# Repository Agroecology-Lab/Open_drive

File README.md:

# Open Drive

Dual-motor BLDC / FOC controller. Compatible with ODrive 3.5 and SimpleFOC.

## Specification

| | |
|---|---|
| Motor channels | 2 (M0, M1), 3-phase each |
| MCU | STM32F405RGT7, LQFP-64, 8 MHz ceramic resonator (Y1) |
| Gate drivers | 2 × DRV8301 (U1 = M0, U2 = M1), SPI-configured |
| Power stage | 12 × IRF7480M DirectFET N-MOSFET (6 per motor) |
| Current sense | 4 × 0.5 mΩ 2512 shunts (R12, R16, R32, R36), DRV8301 amplifiers |
| Supply | XT30 (J3), silk-marked MAX 48 V |
| Bulk capacitance | 10 µF 50 V 1206 array on bottom side |
| Logic supply | 5 V from DRV8301 (U1) buck (L1, D1); 3.3 V from U4 (SPX3819); 3.3 VA analog from U5 (LP5907) |
| USB | USB-C (J4), USBLC6-2SC6 ESD (U8); VBUS via F1 (500 mA) and D4 into +5 V |
| CAN | SN65HVD232 transceiver (U7), two connectors (J7, J8) |
| Auxiliary half-bridge | Q13, Q14 (CSD18540Q5B), LM5109B driver (U3); AUX_H / AUX_L from MCU; switch node `HS` on pad H6 |
| Temperature | 3 × 10 k NTC (TH1–TH3): M0_TEMP, M1_TEMP, AUX_TEMP |
| PCB | 4 layers, 1.6 mm, approx. 85.5 × 56 mm, 4 × mounting holes |
| Assembly | JLCPCB, both sides |

Firmware is not included in this repository.

## Connectors

| Ref | Silk | Type | Pins |
|---|---|---|---|
| J3 | MAX 48V | XT30PW | 1 GND, 2 VDC |
| J1 | M0 | MR30PW 3-pole | phases A, B, C |
| J2 | M1 | MR30PW 3-pole | phases A, B, C |
| J10 | ENC0 | JST SH 5-pin | 1 GND, 2 +5 V, 3 A, 4 B, 5 Z |
| J11 | ENC1 | JST SH 5-pin | 1 GND, 2 +5 V, 3 A, 4 B, 5 Z |
| J4 | USB | USB-C | USB 2.0, DFU / serial via STM32 |
| J5 | Serial | JST SH 3-pin | 1 GPIO_1, 2 GPIO_2, 3 GND |
| J6 | GPIO | JST SH 6-pin | 1–6 = GPIO_3 … GPIO_8 |
| J7 | CAN2 | JST SH 2-pin | 1 CAN_H, 2 CAN_L |
| J8 | CAN1 | JST SH 2-pin | 1 CAN_H, 2 CAN_L |
| J9 | DEBUG | JST SH 4-pin | 1 +5 V, 2 SWDIO, 3 SWCLK, 4 GND |

Bottom side also has solder pads for power (+ / −) and for each motor (U, V, W).

## Indicators and controls

- SW1 (DFU): pulls BOOT0 to 3.3 V. Hold while powering to enter the STM32 DFU bootloader.
- D3: green LED.
- Test pads (top, right): nFAULT, VCC, AVCC, 5V.
- TP4, TP5: test points near J4.

## Schematic

[Open_Drive_Schematic.pdf](Open_Drive_Schematic.pdf). KiCad sheets in `bldc_motor_cntroller/`:

| Sheet | Contents |
|---|---|
| `bldc_motor_cntroller.sch` | Top level |
| `microcontroller_interface.sch` | STM32F405 |
| `motor_driver.sch` | M0 DRV8301 and power stage |
| `motor_driver2.sch` | M1 DRV8301 and power stage |
| `power_management.sch` | Buck, LDOs, auxiliary half-bridge |
| `io_interface.sch` | USB, CAN, encoders, GPIO, debug |

## Repository layout

```
bldc_motor_cntroller/
  *.sch, *.kicad_pcb, *.pro   KiCad project
  outputs/gerbers/            Gerber and drill files
  assembly/                   BOM and placement (KiCad export)
  production/                 JLCPCB BOM, placement, netlist, order zip
  bom/ibom.html               Interactive BOM
  images/                     Board renders
Open_Drive_Schematic.pdf
```

## Ordering

1. Upload `bldc_motor_cntroller/outputs/gerbers/` (or `production/bldc_motor_cntroller.zip`) to JLCPCB, 4 layers, 1.6 mm.
2. Enable assembly, both sides. Upload the BOM and positions files from `production/`.
3. Check part rotation in the JLCPCB PCBA viewer before ordering. Rotation of SW1 and U4 differs from the KiCad export.

## Attribution

Based on [X_driver](https://github.com/dj140/X_driver) by Dj140, which is based on the ODrive 3.5 schematic.

## License

GPL-3.0. See [LICENSE](LICENSE).

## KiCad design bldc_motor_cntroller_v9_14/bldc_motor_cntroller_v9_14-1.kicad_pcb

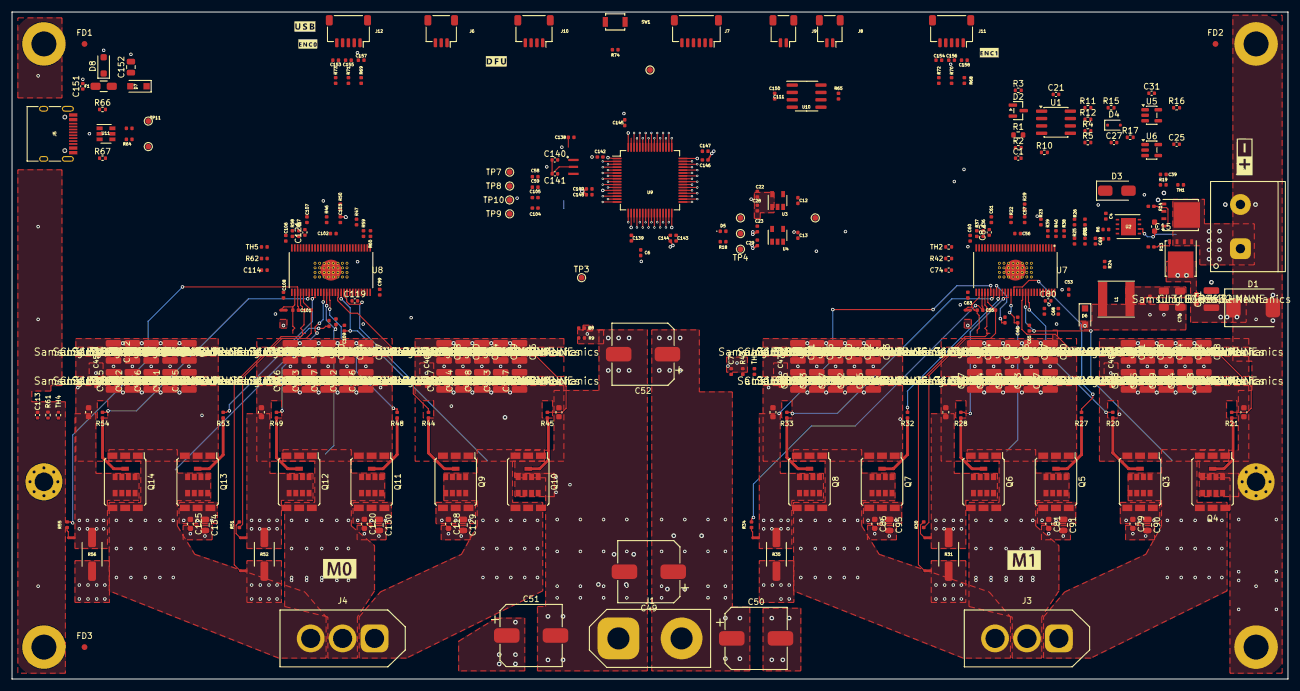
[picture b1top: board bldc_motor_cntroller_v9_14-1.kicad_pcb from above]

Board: 4 copper layers, 220.0 x 115.0 mm, 329 parts (0 on the bottom side), 165 nets.

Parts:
C1: 100pF 50V; C_0402_1005Metric
C2, C3, C5, C7, C8, C9, C10, C11, C14, C16, C17, C18, C19, C20, C24, C26, C30, C32, C33, C34, C35, C36, C37, C38, C40, C41, C42, C43, C44, C71, C76, C77, C78, C83, C84, C85, C87, C88, C89, C92, C93, C94, C96, C97, C98, C112, C115, C116, C117, C122, C123, C124, C126, C127, C128, C131, C132, C133, C135, C136, C137: 4.7uF 100V; C_1210_3225Metric
C4, C57, C74, C75, C103, C113, C114: 2.2uF 25V; C_0402_1005Metric
C6, C73: 270pF 50V; C_0402_1005Metric
C12, C13, C22, C23, C60, C61, C72, C106, C107, C149: 1uF 25V; C_0402_1005Metric
C15: 470nF 50V; C_0603_1608Metric
C21, C25, C31, C138: 100nF 16V; C_0402_1005Metric
C27: 470pF 50V; C_0402_1005Metric
C28, C29: 0.1uF 16V; C_0402_1005Metric
C39, C144, C146: 2.2uF 16V; C_0402_1005Metric
C45, C46, C47, C48, C62, C63, C65, C66, C67, C68, C80, C82, C108, C119, C121, C151: 100nF 50V; C_0402_1005Metric
C49, C50, C51, C52: 100uF 100V; CP_Elec_10x10.5
C53, C99: 15nF 50V; C_0402_1005Metric
C54, C55, C58, C59, C100, C101, C104, C105: 2.2nF 50V; C_0402_1005Metric
C56, C102: 22nF 50V; C_0402_1005Metric
C64, C70: 47uF 16V; C_1206_3216Metric
C69: 82pF 50V; C_0402_1005Metric
C79, C81, C86, C118, C120, C125: 100nF 100V; C_0603_1608Metric
C90, C91, C95, C129, C130, C134: 1uF 100V; C_0805_2012Metric
C109, C110, C111: 0.1uF 50V; C_0402_1005Metric
C139, C142, C143, C145, C147, C148, C150, C153, C154, C155, C156, C157, C158: 100nF; C_0402_1005Metric
C140, C141: 12pF; C_0402_1005Metric
C152: 4.7uF 25V; C_0805_2012Metric
C_AUX1: 100nF 100V; C_0603_1608Metric
C_HF1, C_HF2, C_HF3, C_HF4, C_HF5, C_HF6: 100nF 100V; C_0603_1608Metric
D1: 5.0SMDJ48A; D_SMC
D2: LM4040C25IDBZR; SOT-23
D3: STPS1H100A; D_SMA
D4: BAT54J; D_SOD-323F
D5: GREEN; LED_0402_1005Metric
D6, D7: MBR2H100SFT3G; D_SOD-123F
D8: SMF5.0A; D_SOD-123F
F1: Fuse_500MA; Fuse_1206_3216Metric
FD1, FD2, FD3: Fiducial; Fiducial_1mm_Mask2mm
G1: LOGO; M00
G2: LOGO; M1
G3: LOGO; batt
G4: LOGO; DFU
G5: LOGO; USB
G6: LOGO; ENC0
G7: LOGO; ENC1
H1, H4: MountingHole_3.2mm_M3_Pad_Via
H2, H3, H5, H6: MountingHole_Pad; MountingHole_4.3mm_M4_Pad
J1: XT90; AMASS_XT90-M_1x02_P10.90mm_Vertical
J2: DB910-7.62-2P-GN-S; DORABO_DB910-7.62-2P
J3, J4: MR60PB-M 30A (60A); AMASS_MR60PB-M_1x03_P5.50mm_Vertical
J5: USB_C_Receptacle_USB2.0; USB_C_Receptacle_HRO_TYPE-C-31-M-12
J6: Conn_01x03; JST_SH_SM03B-SRSS-TB_1x03-1MP_P1.00mm_Horizontal
J7: Conn_01x06; JST_SH_SM06B-SRSS-TB_1x06-1MP_P1.00mm_Horizontal
J8, J9: Conn_01x02; JST_SH_SM02B-SRSS-TB_1x02-1MP_P1.00mm_Horizontal
J10: Conn_01x04; JST_SH_SM04B-SRSS-TB_1x04-1MP_P1.00mm_Horizontal
J11, J12: Conn_01x05; JST_SH_SM05B-SRSS-TB_1x05-1MP_P1.00mm_Horizontal
L1: 33uH 1.4A; L_Taiyo-Yuden_NR-60xx
NT1, NT2, NT3, NT4, NT5, NT6, NT7, NT8: Net-Tie_2; NetTie-2_SMD_Pad0.5mm
Q1, Q2: CSD18540Q5B; TDSON-8-1
Q3, Q4, Q5, Q6, Q7, Q8, Q9, Q10, Q11, Q12, Q13, Q14: IRF7759L2TRPBF; DirectFET_L8
R1: 180k; R_0603_1608Metric
R2, R4, R5, R38, R39, R40, R59, R60, R74: 10k; R_0402_1005Metric
R3, R9, R15, R18, R22, R46: 1k; R_0402_1005Metric
R6, R7, R19, R26, R29, R42, R43, R50, R61, R62, R68, R69, R70, R71, R72, R73: 3.3k; R_0402_1005Metric
R8, R23, R25, R47: 18k; R_0402_1005Metric
R10: 330k; R_0402_1005Metric
R11, R12: 4.7k; R_0402_1005Metric
R13, R14, R20, R21, R27, R28, R32, R33, R44, R45, R48, R49, R53, R54: 2R2; R_0402_1005Metric
R16, R17: 100k; R_0402_1005Metric
R24: 220k 1%; R_0402_1005Metric
R30, R34, R51, R55, R65: 120R; R_0402_1005Metric
R31, R35, R52, R56: 500uOhm 6W 1%; R_2512_6332Metric
R36, R37, R57, R58, R63, R64: 22R 1%; R_0402_1005Metric
R41: 47k 1%; R_0402_1005Metric
R66, R67: 5.1k 1%; R_0402_1005Metric
SW1: B3U-1000P-B; SW_SPST_B3U-1000P
TH1, TH2, TH3, TH4, TH5: 10k; R_0402_1005Metric
TP1, TP2, TP3, TP4, TP5, TP6, TP7, TP8, TP9, TP10, TP11, TP12: TestPoint; TestPoint_Pad_D1.0mm
U1: LM393BIDR; SOIC-8_3.9x4.9mm_P1.27mm
U2: LM5109BSD; WSON-8_4x4mm_P0.8mm
U3: SPX3819M5-L-3-3; SOT-23-5
U4: LP5907MFX-3.3; SOT-23-5
U5: SN74LVC1G32DBVR; SOT-23-5
U6: SN74LVC1G08DBVR; SOT-23-5
U7, U8: DRV8301DCAR; DRV8301DCA_v9
U9: STM32F405RGTx; LQFP-64_10x10mm_P0.5mm
U10: SN65HVD232; SOIC-8_3.9x4.9mm_P1.27mm
U11: USBLC6-2SC6; SOT-23-6
Y1: CSTCE8M00G55-R0

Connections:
+3.3V: C21.1, C22.1, C25.1, C28.1, C31.1, C80.1, C119.1, C139.1, C142.1, C143.1, C145.1, C147.1, C150.2, D5.1, R3.1, R4.1, R11.1, R12.1, R38.2, R39.2, R40.2, R59.2, R60.2, R68.1, R69.1, R70.1, R71.1, R72.1, R73.1, SW1.1, TP1.1, U1.8, U3.5, U5.5, U6.5, U7.49, U8.49, U9.1, U9.19, U9.32, U9.48, U9.64, U10.3
+3.3VA: C23.1, C29.1, C82.1, C121.1, C148.1, C149.1, TH1.1, TH2.1, TH3.1, TH4.1, TH5.1, TP2.1, U4.5, U7.24, U8.24, U9.13
+5V: C12.1, C13.1, C64.1, C70.1, C72.1, D7.1, J10.1, J11.2, J12.2, L1.2, R25.2, TP5.1, U3.1, U3.3, U4.1, U4.3, U11.5
/I/O Interface/BOOT0: R74.2, SW1.2, U9.60
/I/O Interface/CAN_D: U9.62, U10.1
/I/O Interface/CAN_R: U9.61, U10.4
/I/O Interface/DEBUG_SWCLK: J10.3, U9.49
/I/O Interface/DEBUG_SWDIO: J10.2, U9.46
/I/O Interface/ENC0_A: C154.2, J11.3, R72.2, U9.56
/I/O Interface/ENC0_B: C156.2, J11.4, R70.2, U9.57
/I/O Interface/ENC0_Z: C158.2, J11.5, R68.2, U9.40
/I/O Interface/ENC1_A: C153.2, J12.3, R73.2, U9.58
/I/O Interface/ENC1_B: C155.2, J12.4, R71.2, U9.59
/I/O Interface/ENC1_Z: C157.2, J12.5, R69.2, U9.4
/I/O Interface/GPIO_1: J6.1, U9.14
/I/O Interface/GPIO_2: J6.2, U9.15
/I/O Interface/GPIO_3: J7.1, U9.16
/I/O Interface/GPIO_4: J7.2, U9.17
/I/O Interface/GPIO_5: J7.3, U9.24
/I/O Interface/GPIO_6: J7.4, U9.28
/I/O Interface/GPIO_7: J7.5, U9.50
/I/O Interface/GPIO_8: J7.6, U9.55
/I/O Interface/USB_CC1: J5.A5, R66.1
/I/O Interface/USB_CC2: J5.B5, R67.1
/I/O Interface/USB_DN: R63.1, TP11.1, U9.44
/I/O Interface/USB_DP: R64.1, TP12.1, U9.45
/I/O Interface/USB_J4_DN: J5.A7, J5.B7, R63.2, U11.1, U11.6
/I/O Interface/USB_J4_DP: J5.A6, J5.B6, R64.2, U11.3, U11.4
/I/O Interface/USB_VBUS_PROT: C152.1, D7.2, D8.1, F1.2
/I/O Interface/USB_VBUS_RAW: C151.1, F1.1, J5.A4, J5.A9, J5.B4, J5.B9
/Microcontroller Interface/AUX_TEMP: C39.1, R19.2, TH1.2, U9.21
/Microcontroller Interface/EN_GATE: R22.2, R46.2, U7.16, U8.16, U9.33
/Microcontroller Interface/M0_AH: U7.17, U9.41
/Microcontroller Interface/M0_AL: U7.18, U9.34
/Microcontroller Interface/M0_BH: U7.19, U9.42
/Microcontroller Interface/M0_BL: U7.20, U9.35
/Microcontroller Interface/M0_CH: U7.21, U9.43
/Microcontroller Interface/M0_CL: U7.22, U9.36
/Microcontroller Interface/M0_SO1: C58.2, R36.2, TP7.1, U9.8
/Microcontroller Interface/M0_SO2: C59.2, R37.2, TP8.1, U9.9
/Microcontroller Interface/M0_TEMP: C75.1, R43.2, TH3.2, U9.25
/Microcontroller Interface/M1_AH: U8.17, U9.37
/Microcontroller Interface/M1_AL: U8.18, U9.23
/Microcontroller Interface/M1_BH: U8.19, U9.38
/Microcontroller Interface/M1_BL: U8.20, U9.26
/Microcontroller Interface/M1_CH: U8.21, U9.39
/Microcontroller Interface/M1_CL: U8.22, U9.27
/Microcontroller Interface/M1_SO1: C104.2, R57.2, TP9.1, U9.11
/Microcontroller Interface/M1_SO2: C105.2, R58.2, TP10.1, U9.10
/Microcontroller Interface/M1_TEMP: C114.1, R62.2, TH5.2, U9.20
/Microcontroller Interface/SPI_M0_nCS: U7.8, U9.2
/Microcontroller Interface/SPI_M1_nCS: U8.8, U9.3
/Microcontroller Interface/SPI_MISO: U7.10, U8.10, U9.52
/Microcontroller Interface/SPI_MOSI: U7.9, U8.9, U9.53
/Microcontroller Interface/SPI_SCK: U7.11, U8.11, U9.51
/Microcontroller Interface/VBUS_S: C6.1, R8.2, R9.1, U9.22
/Microcontroller Interface/nFAULT: R39.1, R59.1, TP6.1, U7.6, U8.6, U9.54
/Motor Driver/AVDD: C60.1, U7.27
/Motor Driver/DVDD: C61.1, U7.23
/Motor Driver/GH_A: R20.1, U7.47
/Motor Driver/GH_B: R27.1, U7.42
/Motor Driver/GH_C: R32.1, U7.37
/Motor Driver/GL_A: R21.1, U7.45
/Motor Driver/GL_B: R28.1, U7.40
/Motor Driver/GL_C: R33.1, U7.35
/Motor Driver/PWRGD: R38.1, U7.4
/Motor Driver/SH_A: C65.1, J3.1, Q3.3, Q4.1, U7.46
/Motor Driver/SH_B: C66.1, J3.2, Q5.3, Q6.1, U7.41
/Motor Driver/SH_C: C67.1, J3.3, Q7.3, Q8.1, U7.36
/Motor Driver/SL_B: C_HF2.2, NT1.2, Q6.3, R31.2, U7.39
/Motor Driver/SL_C: C_HF3.2, NT3.2, Q8.3, R35.2, U7.34
/Motor Driver/SN1: C54.2, R30.1, U7.33
/Motor Driver/SN2: C55.2, R34.1, U7.31
/Motor Driver/SP1: C54.1, NT2.1, U7.32
/Motor Driver/SP2: C55.1, NT4.1, U7.30
/Motor Driver/TEMP_SENSE_2: C74.1, R42.2, TH2.2
/Motor Driver/nOCTW: R40.1, U7.5
/Motor_Driver2/AVDD: C106.1, U8.27
/Motor_Driver2/DVDD: C107.1, U8.23
/Motor_Driver2/GH_A: R44.1, U8.47
/Motor_Driver2/GH_B: R48.1, U8.42
/Motor_Driver2/GH_C: R53.1, U8.37
/Motor_Driver2/GL_A: R45.1, U8.45
/Motor_Driver2/GL_B: R49.1, U8.40
/Motor_Driver2/GL_C: R54.1, U8.35
/Motor_Driver2/SH_A: C109.1, J4.1, Q9.3, Q10.1, U8.46
/Motor_Driver2/SH_B: C110.1, J4.2, Q11.3, Q12.1, U8.41
/Motor_Driver2/SH_C: C111.1, J4.3, Q13.3, Q14.1, U8.36
/Motor_Driver2/SL_B: C_HF5.2, NT5.2, Q12.3, R52.2, U8.39
/Motor_Driver2/SL_C: C_HF6.2, NT7.2, Q14.3, R56.2, U8.34
/Motor_Driver2/SN1: C100.2, R51.1, U8.33
/Motor_Driver2/SN2: C101.2, R55.1, U8.31
/Motor_Driver2/SP1: C100.1, NT6.1, U8.32
/Motor_Driver2/SP2: C101.1, NT8.1, U8.30
/Motor_Driver2/TEMP_SENSE_2: C113.1, R61.2, TH4.2
/Motor_Driver2/nOCTW: R60.1, U8.5
/Power Management/HS: C15.2, J2.1, Q1.1, Q1.2, Q1.3, Q2.5, U2.6
/Power Management/OVP_ACTIVE: D4.1, R10.2, R11.2, R15.1, U1.1, U1.6
/Power Management/OVP_ACTIVE_DLY: C27.1, D4.2, R15.2, U5.2
/Power Management/OVP_VMID: R4.2, R5.1, U1.5
/Power Management/OVP_VREF: D2.1, R3.2, U1.2
/Power Management/OVP_VSENSE: C1.1, R1.2, R2.1, R10.1, U1.3
/Power Management/nOVP_ACTIVE: R12.2, U1.7, U6.2
CAN_H: J8.1, J9.1, R65.2, U10.7
CAN_L: J8.2, J9.2, R65.1, U10.6
GND: C1.2, C2.2, C3.2, C4.2, C5.2, C6.2, C7.2, C8.2, C9.2, C10.2, C11.2, C12.2, C13.2, C14.2, C16.2, C17.2, C18.2, C19.2, C20.2, C21.2, C22.2, C23.2, C24.2, C25.2, C26.2, C27.2, C28.2, C29.2, C30.2, C31.2, C32.2, C33.2, C34.2, C35.2, C36.2, C37.2, C38.2, C39.2, C40.2, C41.2, C42.2, C43.2, C44.2, C45.2, C46.2, C47.2, C48.2, C49.2, C50.2, C51.2, C52.2, C53.1, C57.2, C58.1, C59.1, C60.2, C61.2, C63.2, C64.2, C68.2, C69.2, C70.2, C71.2, C72.2, C73.2, C74.2, C75.2, C76.2, C77.2, C78.2, C79.2, C80.2, C81.2, C82.2, C83.2, C84.2, C85.2, C86.2, C87.2, C88.2, C89.2, C90.2, C91.2, C92.2, C93.2, C94.2, C95.2, C96.2, C97.2, C98.2, C99.1, C103.2, C104.1, C105.1, C106.2, C107.2, C108.2, C112.2, C113.2, C114.2, C115.2, C116.2, C117.2, C118.2, C119.2, C120.2, C121.2, C122.2, C123.2, C124.2, C125.2, C126.2, C127.2, C128.2, C129.2, C130.2, C131.2, C132.2, C133.2, C134.2, C135.2, C136.2, C137.2, C138.2, C139.2, C140.1, C141.1, C142.2, C143.2, C144.2, C145.2, C146.2, C147.2, C148.2, C149.2, C150.1, C151.2, C152.2, C153.1, C154.1, C155.1, C156.1, C157.1, C158.1, C_AUX1.2, C_HF1.2, C_HF4.2, D1.2, D2.2, D6.2, D8.2, H1.1 (1_1), H2.1 (1_1), H3.1 (1_1), H4.1 (1_1), H5.1 (1_1), H6.1 (1_1), J1.1, J2.2, J5.A1, J5.A12, J5.B1, J5.B12, J5.S1, J6.3, J10.4, J11.1, J12.1, NT2.2, NT4.2, NT6.2, NT8.2, Q2.1, Q2.2, Q2.3, Q4.3, Q10.3, R2.2, R5.2, R6.1, R7.1, R9.2, R16.2, R17.2, R18.2, R19.1, R22.1, R23.2, R24.2, R26.1, R29.1, R31.1, R35.1, R42.1, R43.1, R46.1, R47.2, R50.1, R52.1, R56.1, R61.1, R62.1, R66.2, R67.2, R74.1, TP4.1, U1.4, U2.4, U2.9, U3.2, U4.2, U5.3, U6.3, U7.28, U7.44, U7.57, U8.28, U8.44, U8.55, U8.57, U9.12, U9.18, U9.63, U10.2, U11.2, Y1.3
GVDD: C4.1, C57.1, C103.1, D3.2, TP3.1, U2.1, U7.13, U8.13
unnamed: C73.1, R41.2
unnamed: C15.1, D3.1, U2.8
unnamed: D5.2, R18.1
unnamed: C62.1, D6.1, L1.1, U7.50, U7.51
unnamed: NT1.1, R30.2
unnamed: NT3.1, R34.2
unnamed: NT5.1, R51.2
unnamed: NT7.1, R55.2
unnamed: Q1.4, R13.1
unnamed: Q2.4, R14.1
unnamed: Q3.2, R20.2
unnamed: Q4.2, R21.2
unnamed: Q5.2, R27.2
unnamed: Q6.2, R28.2
unnamed: Q7.2, R32.2
unnamed: Q8.2, R33.2
unnamed: Q9.2, R44.2
unnamed: Q10.2, R45.2
unnamed: Q11.2, R48.2
unnamed: Q12.2, R49.2
unnamed: Q13.2, R53.2
unnamed: Q14.2, R54.2
unnamed: R13.2, U2.7
unnamed: R14.2, U2.5
unnamed: C65.2, U7.48
unnamed: C66.2, U7.43
unnamed: C62.2, U7.52
unnamed: C67.2, U7.38
unnamed: C69.1, R41.1, U7.2
unnamed: C56.1, U7.14
unnamed: C56.2, U7.15
unnamed: R29.2, U7.12
unnamed: R23.1, U7.7
unnamed: R24.1, U7.1
unnamed: R36.1, U7.25
unnamed: R37.1, U7.26
unnamed: C53.2, U7.56
unnamed: R25.1, R26.2, U7.3
unnamed: C109.2, U8.48
unnamed: C110.2, U8.43
unnamed: C111.2, U8.38
unnamed: C102.1, U8.14
unnamed: C102.2, U8.15
unnamed: R50.2, U8.12
unnamed: R47.1, U8.7
unnamed: R57.1, U8.25
unnamed: R58.1, U8.26
unnamed: C99.2, U8.56
unnamed: C138.1, U9.7
unnamed: C140.2, U9.5, Y1.1
unnamed: C141.2, U9.6, Y1.2
unnamed: C144.1, U9.31
unnamed: C146.1, U9.47
OVP_IN_HI: R16.1, U5.1, U9.30
OVP_IN_LI: R17.1, U6.1, U9.29
U3_HI_DRV: R6.2, U2.2, U5.4
U3_LI_DRV: R7.2, U2.3, U6.4
VDC: C2.1, C3.1, C5.1, C7.1, C8.1, C9.1, C10.1, C11.1, C14.1, C16.1, C17.1, C18.1, C19.1, C20.1, C24.1, C26.1, C30.1, C32.1, C33.1, C34.1, C35.1, C36.1, C37.1, C38.1, C40.1, C41.1, C42.1, C43.1, C44.1, C45.1, C46.1, C47.1, C48.1, C49.1, C50.1, C51.1, C52.1, C63.1, C68.1, C71.1, C76.1, C77.1, C78.1, C79.1, C81.1, C83.1, C84.1, C85.1, C86.1, C87.1, C88.1, C89.1, C90.1, C91.1, C92.1, C93.1, C94.1, C95.1, C96.1, C97.1, C98.1, C108.1, C112.1, C115.1, C116.1, C117.1, C118.1, C120.1, C122.1, C123.1, C124.1, C125.1, C126.1, C127.1, C128.1, C129.1, C130.1, C131.1, C132.1, C133.1, C134.1, C135.1, C136.1, C137.1, C_AUX1.1, C_HF1.1, C_HF2.1, C_HF3.1, C_HF4.1, C_HF5.1, C_HF6.1, D1.1, J1.2, Q1.5, Q3.1, Q5.1, Q7.1, Q9.1, Q11.1, Q13.1, R1.1, R8.1, U7.29, U7.53, U7.54, U8.29

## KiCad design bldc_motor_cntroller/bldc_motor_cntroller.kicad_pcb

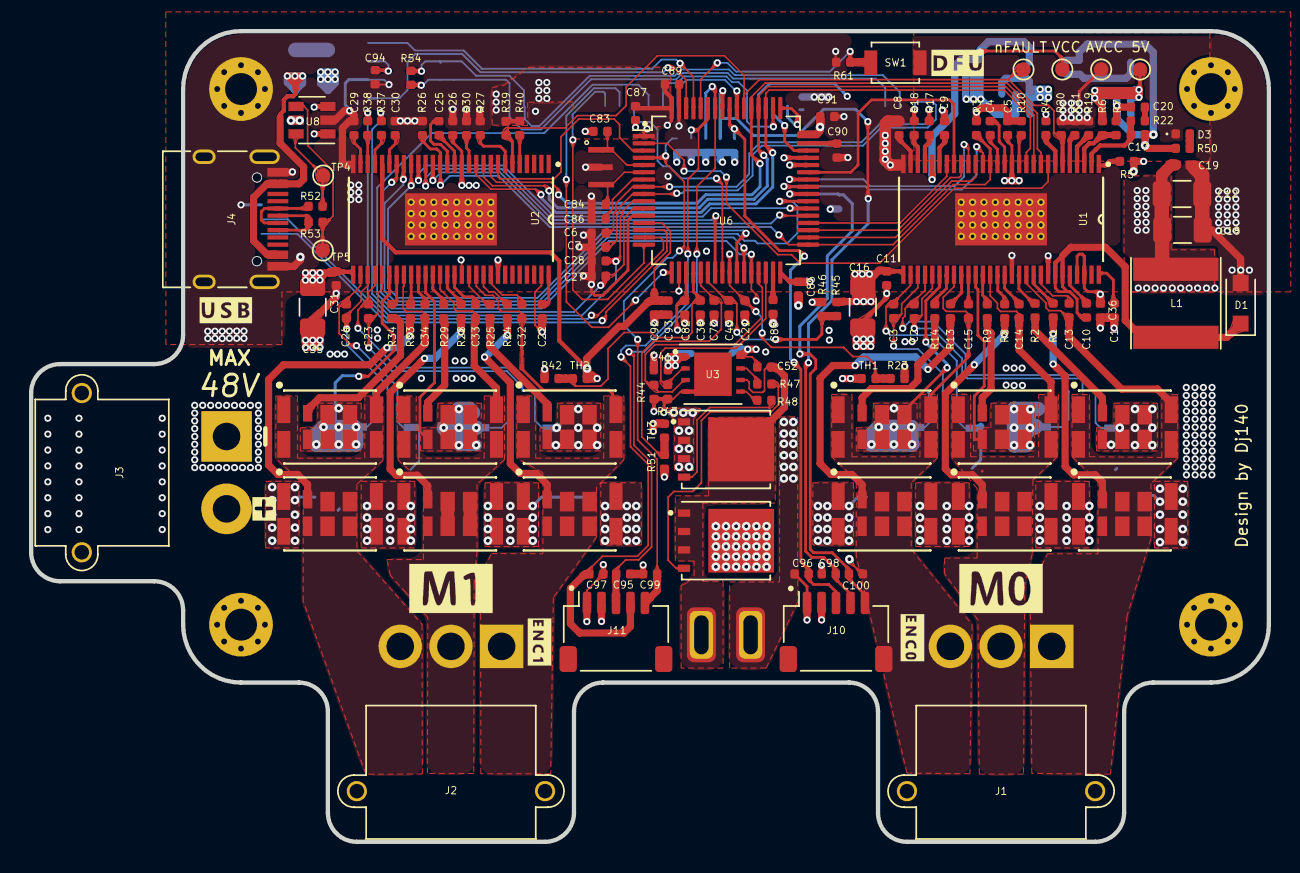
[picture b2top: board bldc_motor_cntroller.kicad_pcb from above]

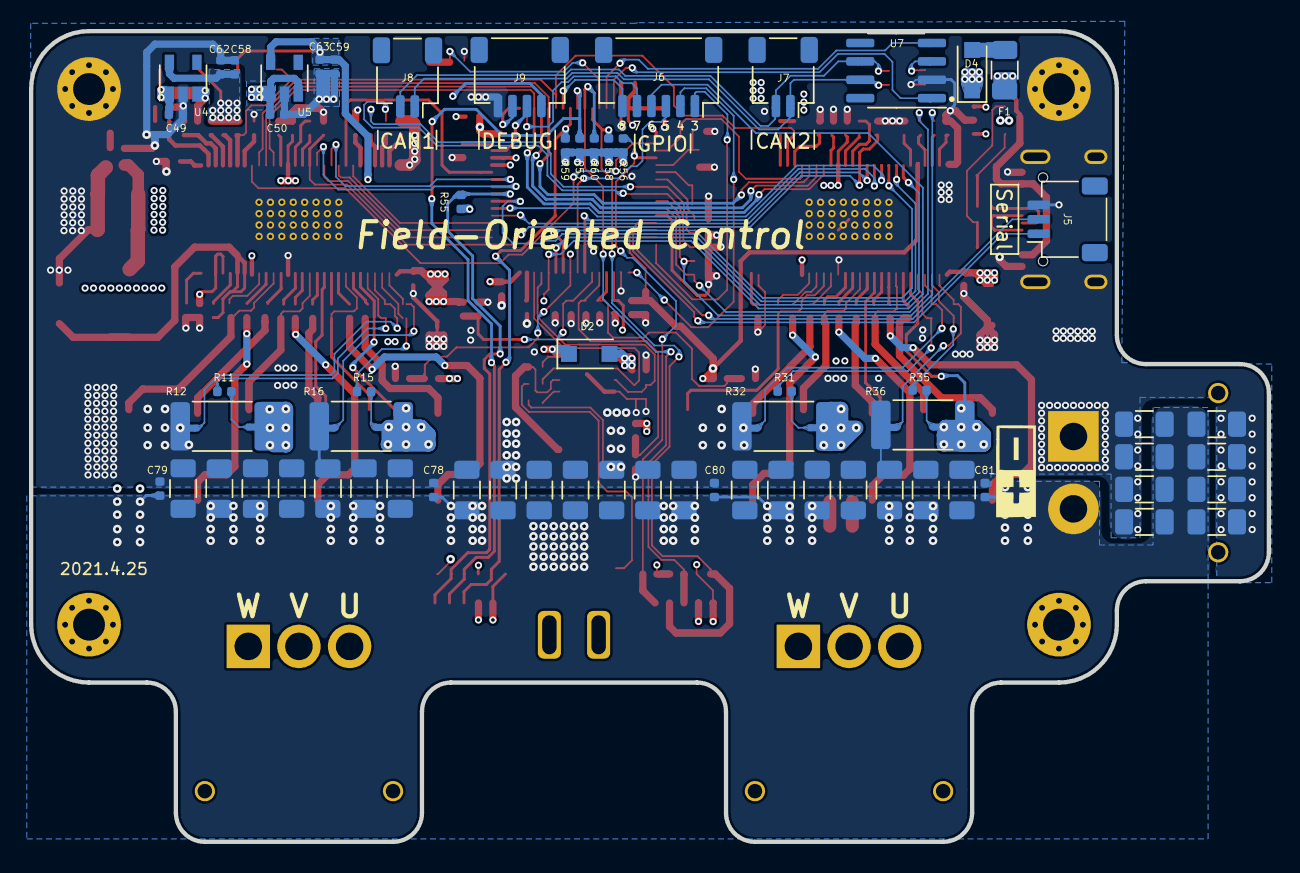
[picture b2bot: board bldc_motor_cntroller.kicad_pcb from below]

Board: 4 copper layers, 85.5 x 56.0 mm, 222 parts (72 on the bottom side), 155 nets.

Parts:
C1, C22: 15nF 50V; C_0402_1005Metric
C2, C3, C6, C7, C23, C24, C27, C28: 2.2nF 50V; C_0402_1005Metric
C4, C25: 22nF 50V; C_0402_1005Metric
C5, C21, C26, C38, C41: 2.2uF 25V; C_0402_1005Metric
C8, C9, C19, C29, C30, C49, C50, C58, C59, C93: 1uF 25V; C_0402_1005Metric
C10, C11, C13, C14, C15, C31, C36, C52, C78, C79, C80, C81: 100nF 50V; C_0402_1005Metric
C12, C18: 47uF 16V; C_1206_3216Metric
C16, C35: 4.7uF 50V; C_1206_3216Metric
C17: 82pF 50V; C_0402_1005Metric
C20, C43: 270pF 50V; C_0402_1005Metric
C32, C33, C34: 0.1uF 50V; C_0402_1005Metric
C39, C40, C42, C44, C45, C46, C47, C48, C51, C53, C54, C55, C56, C57, C60, C61, C64, C65, C66, C67, C68, C69, C70, C71, C73, C74, C75, C76, C77: 100uF 50V; C_1206_3216Metric
C62, C63: 0.1uF 16V; C_0402_1005Metric
C72, C88, C90: 2.2uF 16V; C_0402_1005Metric
C82, C85, C87, C89, C91, C92, C94, C95, C96, C97, C98, C99, C100: 100nF; C_0402_1005Metric
C83, C84: 12pF; C_0402_1005Metric
C86: 100nF 16V; C_0402_1005Metric
D1: 100V 2A SMB; D_SOD-123F
D2: MBR140SFT1G; D_SOD-123F
D3: GREEN; LED_0402_1005Metric
D4: MBR2H100SFT3G; D_SOD-123F
F1: Fuse_500MA; Fuse_1206_3216Metric
H1, H2, H3, H4: MountingHole_Pad; MountingHole_2.2mm_M2_Pad_Via
H5, H6: MountingHole_Pad; TestPoint_Round
J1, J2: MR30PW-M 15A (30A); AMASS_MR30PW-M_1x03_P3.50mm_Horizontal
J3: XT30; AMASS_XT30PW-M_1x02_P2.50mm_Horizontal
J4: USB_C_Receptacle_USB2.0; USB_C_Receptacle_HRO_TYPE-C-31-M-12
J5: Conn_01x03; JST_SH_SM03B-SRSS-TB_1x03-1MP_P1.00mm_Horizontal
J6: Conn_01x06; JST_SH_SM06B-SRSS-TB_1x06-1MP_P1.00mm_Horizontal
J7, J8: Conn_01x02; JST_SH_SM02B-SRSS-TB_1x02-1MP_P1.00mm_Horizontal
J9: Conn_01x04; JST_SH_SM04B-SRSS-TB_1x04-1MP_P1.00mm_Horizontal
J10, J11: Conn_01x05; JST_SH_SM05B-SRSS-TB_1x05-1MP_P1.00mm_Horizontal
L1: 33uH 1.4A; L_Taiyo-Yuden_NR-60xx
NT1, NT2, NT3, NT4, NT5, NT6, NT7, NT8: Net-Tie_2; NetTie-2_SMD_Pad0.5mm
Q1, Q2, Q3, Q4, Q5, Q6, Q7, Q8, Q9, Q10, Q11, Q12: IRF7480MTRPBF; Infineon-MG-WDSON-8-05_2016-901-MFG
Q13, Q14: CSD18540Q5B; TDSON-8-1
R1, R2, R8, R9, R13, R14, R24, R25, R28, R29, R33, R34, R47, R48: 2R2; R_0402_1005Metric
R3, R26, R46, R50: 1k; R_0402_1005Metric
R4, R6, R27, R45: 18k; R_0402_1005Metric
R5: 220k 1%; R_0402_1005Metric
R7, R10, R23, R30, R42, R43, R44, R51, R55, R56, R57, R58, R59, R60: 3.3k; R_0402_1005Metric
R11, R15, R31, R35, R54: 120R; R_0402_1005Metric
R12, R16, R32, R36: 500uOhm 6W 1%; R_2512_6332Metric
R17, R18, R37, R38, R52, R53: 22R 1%; R_0402_1005Metric
R19, R20, R21, R39, R40, R61: 10k; R_0402_1005Metric
R22: 47k 1%; R_0402_1005Metric
SW1: B3U-1000P-B; SW_SPST_B3U-1000P
TH1, TH2, TH3: 10k; R_0402_1005Metric
TP1, TP2, TP3, TP4, TP5, TP6: TestPoint; TestPoint_Pad_D1.0mm
U1, U2: DRV8301DCAR; DRV8301DCA
U3: LM5109BSD; WSON-8_4x4mm_P0.8mm
U4: SPX3819M5-L-3-3; SOT-23-5
U5: LP5907MFX-3.3; SOT-23-5
U6: STM32F405RGTx; LQFP-64_10x10mm_P0.5mm
U7: SN65HVD232; SOIC-8_3.9x4.9mm_P1.27mm
U8: USBLC6-2SC6; SOT-23-6
Y1: Crystal_GND3_Small; CSTCE8M00G55-R0

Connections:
+3.3VA: C59.1, C63.1, C92.1, C93.1, TH1.1, TH2.1, TH3.1, TP3.1, U1.24, U2.24, U5.5, U6.13
+3V3: C58.1, C62.1, C82.1, C85.1, C87.1, C89.1, C91.1, C94.2, D3.1, R19.2, R20.2, R21.2, R39.2, R40.2, R55.1, R56.1, R57.1, R58.1, R59.1, R60.1, SW1.1, TP2.1, U1.49, U2.49, U4.5, U6.1, U6.19, U6.32, U6.48, U6.64, U7.3
+5V: C12.1, C18.1, C19.1, C49.1, C50.1, D4.1, J9.1, J10.2, J11.2, L1.2, R6.2, TP1.1, U4.1, U4.3, U5.1, U5.3, U8.5
/I/O Interface/BOOT0: R61.2, SW1.2, U6.60
/I/O Interface/CAN_D: U6.62, U7.1
/I/O Interface/CAN_R: U6.61, U7.4
/I/O Interface/DEBUG_SWCLK: J9.3, U6.49
/I/O Interface/DEBUG_SWDIO: J9.2, U6.46
/I/O Interface/ENC0_A: C96.2, J10.3, R59.2, U6.56
/I/O Interface/ENC0_B: C98.2, J10.4, R57.2, U6.57
/I/O Interface/ENC0_Z: C100.2, J10.5, R55.2, U6.40
/I/O Interface/ENC1_A: C95.2, J11.3, R60.2, U6.58
/I/O Interface/ENC1_B: C97.2, J11.4, R58.2, U6.59
/I/O Interface/ENC1_Z: C99.2, J11.5, R56.2, U6.4
/I/O Interface/GPIO_1: J5.1, U6.14
/I/O Interface/GPIO_2: J5.2, U6.15
/I/O Interface/GPIO_3: J6.1, U6.16
/I/O Interface/GPIO_4: J6.2, U6.17
/I/O Interface/GPIO_5: J6.3, U6.24
/I/O Interface/GPIO_6: J6.4, U6.28
/I/O Interface/GPIO_7: J6.5, U6.50
/I/O Interface/GPIO_8: J6.6, U6.55
/I/O Interface/USB_D+: R53.1, TP5.1, U8.4
/I/O Interface/USB_D-: R52.1, TP4.1, U8.6
/I/O Interface/USB_DN: U6.44, U8.1
/I/O Interface/USB_DP: U6.45, U8.3
/Microcontroller Interface/AUX_H: R43.2, U3.2, U6.30
/Microcontroller Interface/AUX_L: R44.2, U3.3, U6.29
/Microcontroller Interface/AUX_TEMP: C72.1, R51.2, TH3.2, U6.21
/Microcontroller Interface/EN_GATE: R3.2, R26.2, U1.16, U2.16, U6.33
/Microcontroller Interface/M0_AH: U1.17, U6.41
/Microcontroller Interface/M0_AL: U1.18, U6.34
/Microcontroller Interface/M0_BH: U1.19, U6.42
/Microcontroller Interface/M0_BL: U1.20, U6.35
/Microcontroller Interface/M0_CH: U1.21, U6.43
/Microcontroller Interface/M0_CL: U1.22, U6.36
/Microcontroller Interface/M0_TEMP: C21.1, R23.2, TH1.2, U6.25
/Microcontroller Interface/M1_AH: U2.17, U6.37
/Microcontroller Interface/M1_AL: U2.18, U6.23
/Microcontroller Interface/M1_BH: U2.19, U6.38
/Microcontroller Interface/M1_BL: U2.20, U6.26
/Microcontroller Interface/M1_CH: U2.21, U6.39
/Microcontroller Interface/M1_CL: U2.22, U6.27
/Microcontroller Interface/M1_TEMP: C38.1, R42.2, TH2.2, U6.20
/Microcontroller Interface/SPI_M0_nCS: U1.8, U6.2
/Microcontroller Interface/SPI_M1_nCS: U2.8, U6.3
/Microcontroller Interface/SPI_MISO: U1.10, U2.10, U6.52
/Microcontroller Interface/SPI_MOSI: U1.9, U2.9, U6.53
/Microcontroller Interface/SPI_SCK: U1.11, U2.11, U6.51
/Microcontroller Interface/VBUS_S: C43.1, R45.2, R46.1, U6.22
/Microcontroller Interface/nFAULT: R20.1, R39.1, TP6.1, U1.6, U2.6, U6.54
/Motor Driver/AVDD: C8.1, U1.27
/Motor Driver/CSENSE_1: C6.2, R17.2, U6.8
/Motor Driver/CSENSE_2: C7.2, R18.2, U6.9
/Motor Driver/DVDD: C9.1, U1.23
/Motor Driver/GH_A: R1.1, U1.47
/Motor Driver/GH_B: R8.1, U1.42
/Motor Driver/GH_C: R13.1, U1.37
/Motor Driver/GL_A: R2.1, U1.45
/Motor Driver/GL_B: R9.1, U1.40
/Motor Driver/GL_C: R14.1, U1.35
/Motor Driver/PWRGD: R19.1, U1.4
/Motor Driver/SH_A: C13.1, J1.1, Q1.3, Q1.4, Q1.5, Q1.6, Q1.8, Q2.1, Q2.2, Q2.9, Q2.10, U1.46
/Motor Driver/SH_B: C14.1, J1.2, Q3.3, Q3.4, Q3.5, Q3.6, Q3.8, Q4.1, Q4.2, Q4.9, Q4.10, U1.41
/Motor Driver/SH_C: C15.1, J1.3, Q5.3, Q5.4, Q5.5, Q5.6, Q5.8, Q6.1, Q6.2, Q6.9, Q6.10, U1.36
/Motor Driver/SL_B: NT1.2, Q4.3, Q4.4, Q4.5, Q4.6, Q4.8, R12.2, U1.39
/Motor Driver/SL_C: NT3.2, Q6.3, Q6.4, Q6.5, Q6.6, Q6.8, R16.2, U1.34
/Motor Driver/SN1: C2.2, R11.1, U1.33
/Motor Driver/SN2: C3.2, R15.1, U1.31
/Motor Driver/SP1: C2.1, NT2.1, U1.32
/Motor Driver/SP2: C3.1, NT4.1, U1.30
/Motor Driver/nOCTW: R21.1, U1.5
/Motor_Driver2/AVDD: C29.1, U2.27
/Motor_Driver2/CSENSE_1: C27.2, R37.2, U6.11
/Motor_Driver2/CSENSE_2: C28.2, R38.2, U6.10
/Motor_Driver2/DVDD: C30.1, U2.23
/Motor_Driver2/GH_A: R24.1, U2.47
/Motor_Driver2/GH_B: R28.1, U2.42
/Motor_Driver2/GH_C: R33.1, U2.37
/Motor_Driver2/GL_A: R25.1, U2.45
/Motor_Driver2/GL_B: R29.1, U2.40
/Motor_Driver2/GL_C: R34.1, U2.35
/Motor_Driver2/SH_A: C32.1, J2.1, Q7.3, Q7.4, Q7.5, Q7.6, Q7.8, Q8.1, Q8.2, Q8.9, Q8.10, U2.46
/Motor_Driver2/SH_B: C33.1, J2.2, Q9.3, Q9.4, Q9.5, Q9.6, Q9.8, Q10.1, Q10.2, Q10.9, Q10.10, U2.41
/Motor_Driver2/SH_C: C34.1, J2.3, Q11.3, Q11.4, Q11.5, Q11.6, Q11.8, Q12.1, Q12.2, Q12.9, Q12.10, U2.36
/Motor_Driver2/SL_B: NT5.2, Q10.3, Q10.4, Q10.5, Q10.6, Q10.8, R32.2, U2.39
/Motor_Driver2/SL_C: NT7.2, Q12.3, Q12.4, Q12.5, Q12.6, Q12.8, R36.2, U2.34
/Motor_Driver2/SN1: C23.2, R31.1, U2.33
/Motor_Driver2/SN2: C24.2, R35.1, U2.31
/Motor_Driver2/SP1: C23.1, NT6.1, U2.32
/Motor_Driver2/SP2: C24.1, NT8.1, U2.30
/Motor_Driver2/nOCTW: R40.1, U2.5
/Power Management/HS: C52.2, H6.1, Q13.1, Q13.2, Q13.3, Q14.5, U3.6
CAN_H: J7.1, J8.1, R54.2, U7.7
CAN_L: J7.2, J8.2, R54.1, U7.6
GND: C1.1, C5.2, C6.1, C7.1, C8.2, C9.2, C11.2, C12.2, C16.2, C17.2, C18.2, C19.2, C20.2, C21.2, C22.1, C26.2, C27.1, C28.1, C29.2, C30.2, C31.2, C35.2, C36.2, C38.2, C39.2, C40.2, C41.2, C42.2, C43.2, C44.2, C45.2, C46.2, C47.2, C48.2, C49.2, C50.2, C51.2, C53.2, C54.2, C55.2, C56.2, C57.2, C58.2, C59.2, C60.2, C61.2, C62.2, C63.2, C64.2, C65.2, C66.2, C67.2, C68.2, C69.2, C70.2, C71.2, C72.2, C73.2, C74.2, C75.2, C76.2, C77.2, C78.2, C79.2, C80.2, C81.2, C82.2, C83.1, C84.1, C85.2, C86.2, C87.2, C88.2, C89.2, C90.2, C91.2, C92.2, C93.2, C94.1, C95.1, C96.1, C97.1, C98.1, C99.1, C100.1, D1.2, H1.1, H2.1, H3.1, H4.1, H5.1, J3.1, J4.A1, J4.A12, J4.B1, J4.B12, J4.S1, J5.3, J9.4, J10.1, J11.1, NT2.2, NT4.2, NT6.2, NT8.2, Q2.3, Q2.4, Q2.5, Q2.6, Q2.8, Q8.3, Q8.4, Q8.5, Q8.6, Q8.8, Q14.1, Q14.2, Q14.3, R3.1, R4.2, R5.2, R7.1, R10.1, R12.1, R16.1, R23.1, R26.1, R27.2, R30.1, R32.1, R36.1, R42.1, R43.1, R44.1, R46.2, R50.2, R51.1, R61.1, U1.28, U1.44, U1.57, U1.V, U2.28, U2.44, U2.55, U2.57, U2.V, U3.4, U3.9, U4.2, U5.2, U6.12, U6.18, U6.63, U7.2, U8.2, Y1.3
GVDD: C5.1, C26.1, C41.1, D2.2, U1.13, U2.13, U3.1
unnamed: C1.2, U1.56
unnamed: C4.1, U1.14
unnamed: C4.2, U1.15
unnamed: C10.1, D1.1, L1.1, U1.50, U1.51
unnamed: C10.2, U1.52
unnamed: C13.2, U1.48
unnamed: C14.2, U1.43
unnamed: C15.2, U1.38
unnamed: C17.1, R22.1, U1.2
unnamed: C20.1, R22.2
unnamed: C22.2, U2.56
unnamed: C25.1, U2.14
unnamed: C25.2, U2.15
unnamed: C32.2, U2.48
unnamed: C33.2, U2.43
unnamed: C34.2, U2.38
unnamed: C52.1, D2.1, U3.8
unnamed: C83.2, U6.5, Y1.1
unnamed: C84.2, U6.6, Y1.2
unnamed: C86.1, U6.7
unnamed: C88.1, U6.31
unnamed: C90.1, U6.47
unnamed: D3.2, R50.1
unnamed: D4.2, F1.2
unnamed: F1.1, J4.A4, J4.A9, J4.B4, J4.B9
unnamed: J4.A6, J4.B6, R53.2
unnamed: J4.A7, J4.B7, R52.2
unnamed: NT1.1, R11.2
unnamed: NT3.1, R15.2
unnamed: NT5.1, R31.2
unnamed: NT7.1, R35.2
unnamed: Q1.7, R1.2
unnamed: Q2.7, R2.2
unnamed: Q3.7, R8.2
unnamed: Q4.7, R9.2
unnamed: Q5.7, R13.2
unnamed: Q6.7, R14.2
unnamed: Q7.7, R24.2
unnamed: Q8.7, R25.2
unnamed: Q9.7, R28.2
unnamed: Q10.7, R29.2
unnamed: Q11.7, R33.2
unnamed: Q12.7, R34.2
unnamed: Q13.4, R47.1
unnamed: Q14.4, R48.1
unnamed: R4.1, U1.7
unnamed: R5.1, U1.1
unnamed: R6.1, R7.2, U1.3
unnamed: R10.2, U1.12
unnamed: R17.1, U1.25
unnamed: R18.1, U1.26
unnamed: R27.1, U2.7
unnamed: R30.2, U2.12
unnamed: R37.1, U2.25
unnamed: R38.1, U2.26
unnamed: R47.2, U3.7
unnamed: R48.2, U3.5
VDC: C11.1, C16.1, C31.1, C35.1, C36.1, C39.1, C40.1, C42.1, C44.1, C45.1, C46.1, C47.1, C48.1, C51.1, C53.1, C54.1, C55.1, C56.1, C57.1, C60.1, C61.1, C64.1, C65.1, C66.1, C67.1, C68.1, C69.1, C70.1, C71.1, C73.1, C74.1, C75.1, C76.1, C77.1, C78.1, C79.1, C80.1, C81.1, J3.2, Q1.1, Q1.2, Q1.9, Q1.10, Q3.1, Q3.2, Q3.9, Q3.10, Q5.1, Q5.2, Q5.9, Q5.10, Q7.1, Q7.2, Q7.9, Q7.10, Q9.1, Q9.2, Q9.9, Q9.10, Q11.1, Q11.2, Q11.9, Q11.10, Q13.5, R45.1, U1.29, U1.53, U1.54, U2.29

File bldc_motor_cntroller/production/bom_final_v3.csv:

Designator,Footprint,Quantity,Value,LCSC Part #
"C1, C22",0402,2,15nF 50V,C114405
"C10, C11, C13, C14, C15, C31, C36, C52, C78, C79, C80, C81",0402,12,100nF 50V,C131394
"C100, C82, C85, C87, C89, C91, C92, C94, C95, C96, C97, C98, C99",0402,13,100nF,C131394
"C12, C18",1206,2,47uF 16V,C76659
"C16, C35",1206,2,4.7uF 50V,C51205
C17,0402,1,82pF 50V,C1555
"C19, C29, C30, C49, C50, C58, C59, C8, C9, C93",0402,10,1uF 25V,C52923
"C2, C23, C24, C27, C28, C3, C6, C7",0402,8,2.2nF 50V,C1531
"C20, C43",0402,2,270pF 50V,C541471
"C21, C26, C38, C41, C5",0402,5,2.2uF 25V,C1555
"C25, C4",0402,2,22nF 50V,C1532
"C32, C33, C34",0402,3,0.1uF 50V,C131394
"C39, C40, C42, C44, C45, C46, C47, C48, C51, C53, C54, C55, C56, C57, C60, C61, C64, C65, C66, C67, C68, C69, C70, C71, C73, C74, C75, C76, C77",1206,29,100uF 50V,C93194
"C62, C63",0402,2,0.1uF 16V,C141382
"C72, C88, C90",0402,3,2.2uF 16V,C1555
"C83, C84",0402,2,12pF,C555399
C86,0402,1,100nF 16V,C60474
D1,D_SOD-123F,1,100V 2A SMB,C705302
D2,D_SOD-123F,1,MBR140SFT1G,C52754461
D3,0402,1,GREEN,C74338
D4,D_SOD-123F,1,MBR2H100SFT3G,C16197290
F1,1206,1,Fuse_500MA,C2984676
"H5, H6",TestPoint_Round,2,MountingHole_Pad,N/A
"J1, J2",AMASS_MR30PW-M_1x03_P3.50mm_Horizontal,2,MR30PW-M 15A (30A),C19268034
"J10, J11",JST_SH_SM05B-SRSS-TB_1x05-1MP_P1.00mm_Horizontal,2,Conn_01x05,C136657
J3,AMASS_XT30PW-M_1x02_P2.50mm_Horizontal,1,XT30,C431092
J4,USB_C_Receptacle_HRO_TYPE-C-31-M-12,1,USB_C_Receptacle_USB2.0,C165948
J5,JST_SH_SM03B-SRSS-TB_1x03-1MP_P1.00mm_Horizontal,1,Conn_01x03,C160403
J6,JST_SH_SM06B-SRSS-TB_1x06-1MP_P1.00mm_Horizontal,1,Conn_01x06,C160405
"J7, J8",JST_SH_SM02B-SRSS-TB_1x02-1MP_P1.00mm_Horizontal,2,Conn_01x02,C160402
J9,JST_SH_SM04B-SRSS-TB_1x04-1MP_P1.00mm_Horizontal,1,Conn_01x04,C160404
L1,L_Taiyo-Yuden_NR-60xx,1,33uH 1.4A,C92942
"Q1, Q10, Q11, Q12, Q2, Q3, Q4, Q5, Q6, Q7, Q8, Q9",Infineon-MG-WDSON-8-05_2016-901-MFG,12,IRF7480MTRPBF,C152356
"Q13, Q14",TDSON-8-1,2,CSD18540Q5B,C86513
"R1, R13, R14, R2, R24, R25, R28, R29, R33, R34, R47, R48, R8, R9",0402,14,2R2,C25158
"R10, R23, R30, R42, R43, R44, R51, R55, R56, R57, R58, R59, R60, R7",0402,14,3.3k,C137992
"R11, R15, R31, R35, R54",0402,5,120R,C3015760
"R12, R16, R32, R36",2512,4,500uOhm 6W 1%,C4175647
"R17, R18, R37, R38, R52, R53",0402,6,22R 1%,C482107
"R19, R20, R21, R39, R40, R61, TH1, TH2, TH3",0402,9,10k,C25076
R22,0402,1,47k 1%,C25091
"R26, R3, R46, R50",0402,4,1k,C11702
"R27, R4, R45, R6",0402,4,18k,C497126
R5,0402,1,220k 1%,C3015902
SW1,SW_SPST_B3U-1000P,1,B3U-1000P-B,C231329
"U1, U2",DRV8301DCA,2,DRV8301DCAR,C98969
U3,WSON-8_4x4mm_P0.8mm,1,LM5109BSD,C544701
U4,SOT-23-5,1,SPX3819M5-L-3-3,C9055
U5,SOT-23-5,1,LP5907MFX-3.3,C80670
U6,LQFP-64_10x10mm_P0.5mm,1,STM32F405RGTx,C15742
U7,SOIC-8_3.9x4.9mm_P1.27mm,1,SN65HVD232,C177182
U8,SOT-23-6,1,USBLC6-2SC6,C7519
Y1,CSTCE8M00G55-R0,1,Crystal_GND3_Small,C341522

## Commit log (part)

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2026-01-03 Added recent JLC production files
    Untested as yet
2026-01-03 Added images of board
2026-01-03 Revise README for Open Drive project
    Updated project name and added description and images.
2026-01-04 PDF schematic

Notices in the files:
parts and their libraries:
Copyright 2016 Accelerated Designs. All rights reserved.
